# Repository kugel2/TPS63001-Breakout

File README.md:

# TPS63001-Breakout
Breakoutboard 21x20mm for TPS63001 Buck-Boost Converter

**_Warning_: this board is untested! Use at your own risk!**

Buck-Boost Converter
Vin 1,8-5,5V
Vout 3,3V
Iout max 800mA

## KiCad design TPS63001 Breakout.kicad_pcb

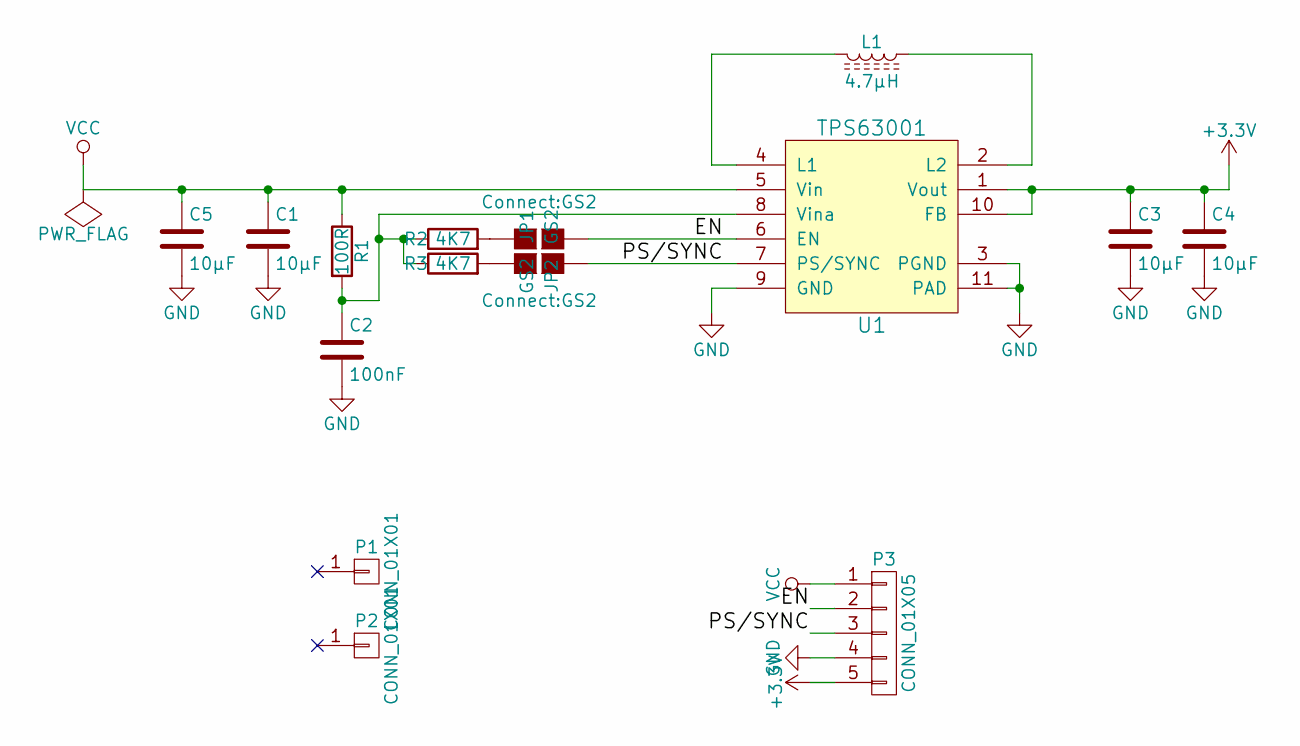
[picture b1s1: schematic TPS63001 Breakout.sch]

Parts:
C1, C3, C4, C5: 10µF; C_1206
C2: 100nF; C_0805
JP1, JP2: GS2
L1: 4.7µH; SRN4026
P1, P2: CONN_01X01; MountingHole_3.2mm_M3_DIN965_Pad
P3: CONN_01X05; Pin_Header_Straight_1x05_Pitch2.54mm
R1: 100R; R_0805
R2, R3: 4K7; R_0805
U1: TPS63001; DFN-10-1EP_3x3mm_Pitch0.5mm

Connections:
+3V3: C3.1, C4.1, P3.5, U1.1 (Vout), U1.10 (FB)
/EN: JP1.2 (G2), P3.2, U1.6 (EN)
/PS/SYNC: JP2.2 (G2), P3.3, U1.7 (PS/SYNC)
GND: C1.2, C2.2, C3.2, C4.2, C5.2, P3.4, U1.3 (PGND), U1.9 (GND), U1.11 (PAD)
unnamed: C2.1, R1.2, R2.1, R3.1, U1.8 (Vina)
unnamed: JP1.1 (G1), R2.2
unnamed: JP2.1 (G1), R3.2
unnamed: L1.1, U1.2 (L2)
unnamed: L1.2, U1.4 (L1)
VCC: C1.1, C5.1, P3.1, R1.1, U1.5 (Vin)

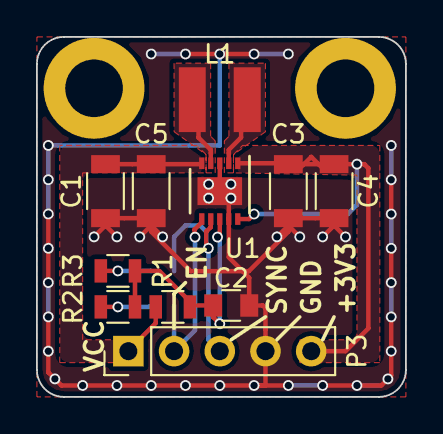
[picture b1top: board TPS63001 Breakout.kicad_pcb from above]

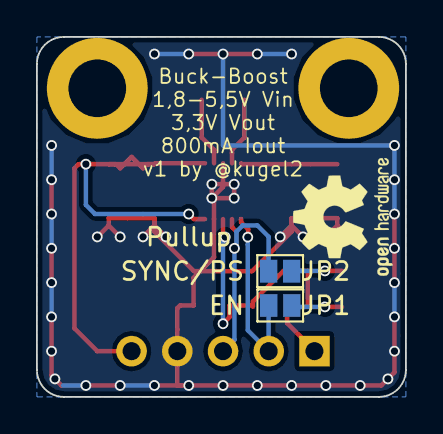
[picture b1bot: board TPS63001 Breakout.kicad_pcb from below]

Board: 2 copper layers, 20.5 x 20.0 mm, 15 parts (2 on the bottom side), 10 nets.

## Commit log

2017-04-08 change pullups for PS/SYNC and EN to VCCA filtered supply
2017-04-08 3d pictures of board
2017-04-08 Update README.md
    add 3d rendering to readme
2017-04-09 silkscreen improvements
2017-04-09 add gerber and pdf
2017-04-09 update pictures
